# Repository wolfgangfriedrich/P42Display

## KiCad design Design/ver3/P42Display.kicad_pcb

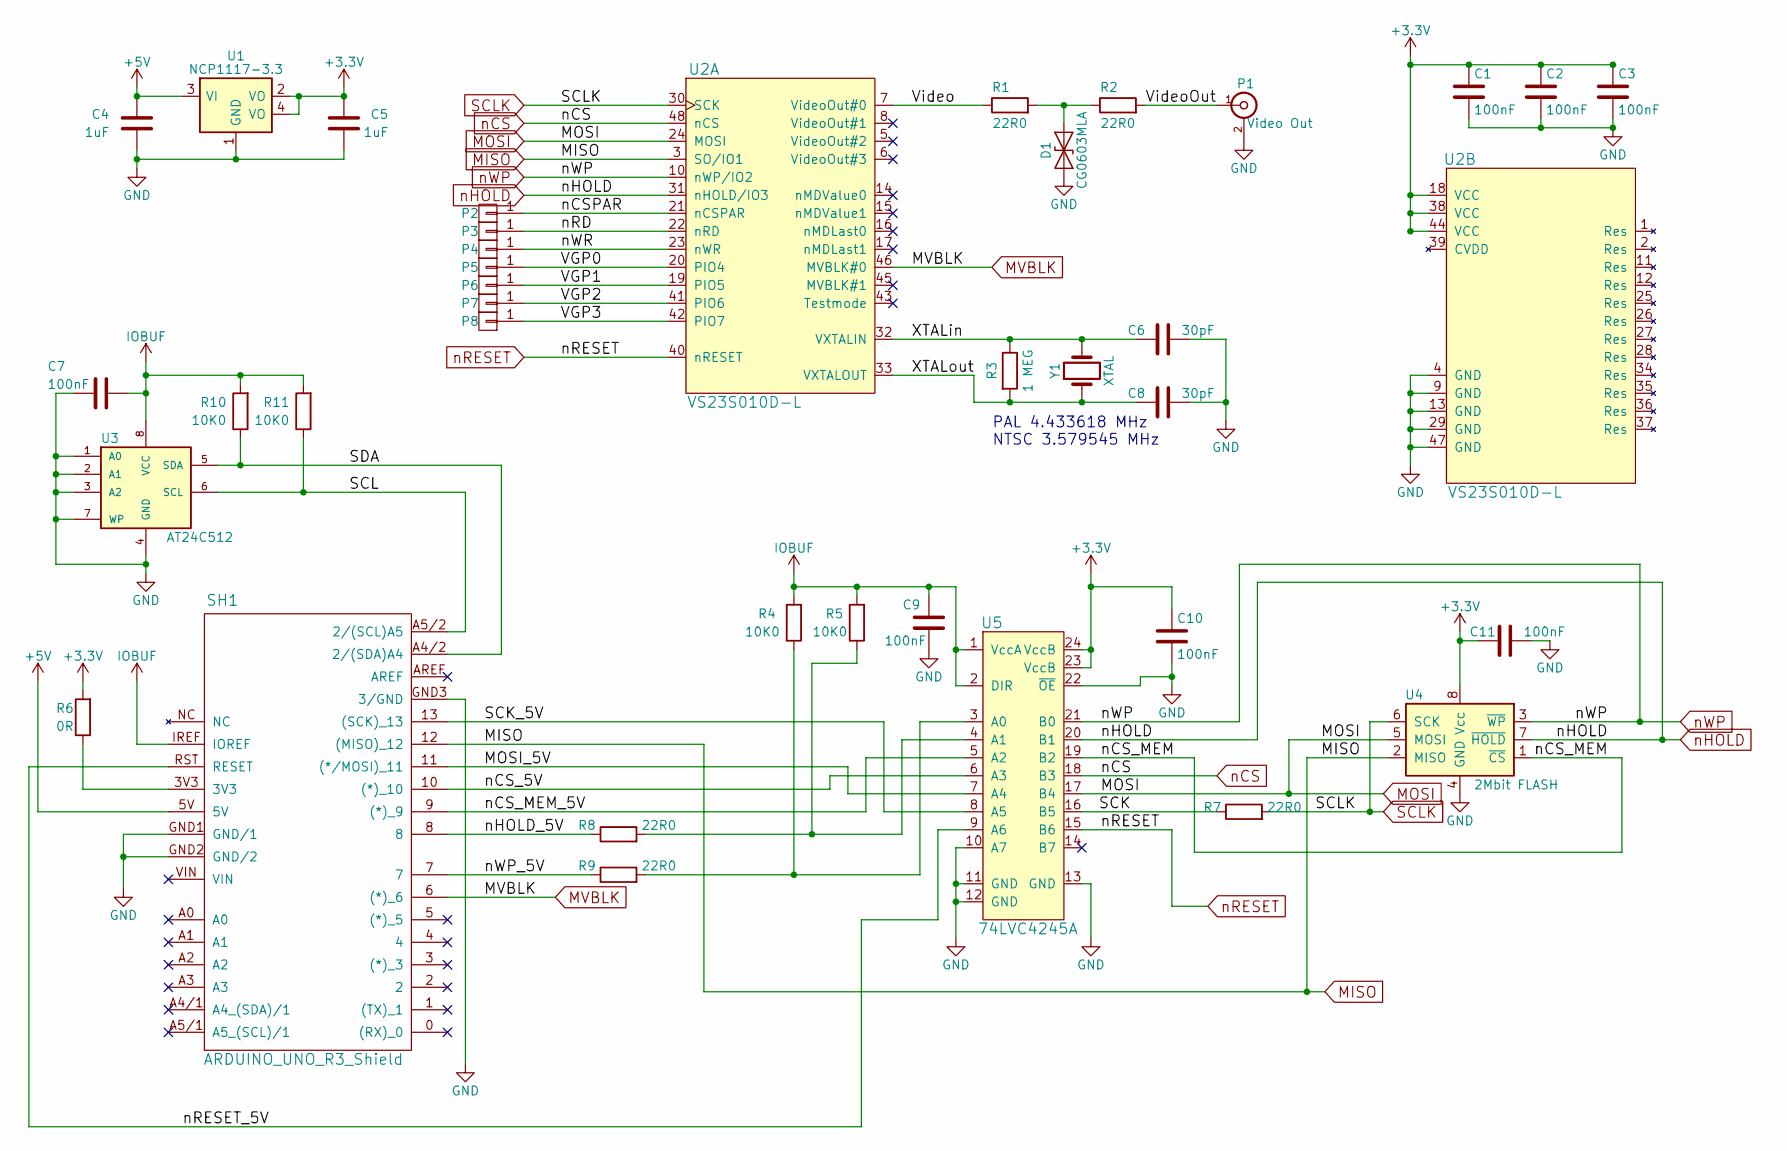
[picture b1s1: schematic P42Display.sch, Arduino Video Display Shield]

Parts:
C1, C2, C3, C7, C9, C10, C11: 100nF; C_0603; Mfr1PN na
C4, C5: 1uF; C_0603; Mfr1PN na
C6, C8: 30pF; C_0603; Mfr1PN na
D1: CG0603MLA; C_0603; Mfr1PN CG0603MLA-5.5ME
P1: Video Out; CUI_RCJ-01x; Mfr1PN RCJ-014
P2: nCS; Measurement_Point_Round-TH_Small
P3: nRD; Measurement_Point_Round-TH_Small
P4: nWR; Measurement_Point_Round-TH_Small
P5: VGP0; Measurement_Point_Round-TH_Small
P6: VGP1; Measurement_Point_Round-TH_Small
P7: VGP2; Measurement_Point_Round-TH_Small
P8: VGP3; Measurement_Point_Round-TH_Small
R1, R2, R7, R8, R9: 22R0; R_0603
R3: 1 MEG; R_0603
R4, R5, R10, R11: 10K0; R_0603
R6: 0R; R_0603
SH1: ARDUINO_UNO_R3_Shield; ARDUINO_as_UNO_R3_CONTOUR
U1: NCP1117-3.3; SOT-223; Mfr1PN AZ1117EH-3.3TRG1
U2: VS23S010D-L; LQFP-48_7x7mm_Pitch0.5mm; Mfr1PN VS23S010D-L
U3: AT24C512; SOIC-8-N; Mfr1PN AT24CS64-SSHM
U4: 2Mbit FLASH; SOIC-8-N; Mfr1PN W25X20CLSNIG
U5: 74LVC4245A; TSSOP-24_4.4x7.8mm_Pitch0.65mm; Mfr1PN 74LVC4245APW
Y1: XTAL; Crystal_SMD_HC49-SD; Mfr1PN ABLS-3.579545MHZ-D-4-T

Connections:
+3V3: C1.1, C2.1, C3.1, C5.2, C10.1, C11.2, R6.2, U1.2 (VO), U1.4 (VO), U2.18 (VCC), U2.38 (VCC), U2.44 (VCC), U4.8 (Vcc), U5.23 (VccB), U5.24 (VccB)
+5V: C4.2, SH1.5V, U1.3 (VI)
/MOSI_5V: SH1.11 ((*/MOSI)_11), U5.7 (A4)
/SCK: R7.1, U5.16 (B5)
/SCK_5V: SH1.13 ((SCK)_13), U5.8 (A5)
/SCL: R11.1, SH1.A5/2 (2/(SCL)A5), U3.6 (SCL)
/SDA: R10.1, SH1.A4/2 (2/(SDA)A4), U3.5 (SDA)
/VGP0: P5.1, U2.20 (PIO4)
/VGP1: P6.1, U2.19 (PIO5)
/VGP2: P7.1, U2.41 (PIO6)
/VGP3: P8.1, U2.42 (PIO7)
/Video: R1.1, U2.7 (VideoOut#0)
/VideoOut: P1.1 (In), R2.2
/XTALin: C6.2, R3.1, U2.32 (VXTALIN), Y1.2
/XTALout: C8.2, R3.2, U2.33 (VXTALOUT), Y1.1
/nCSPAR: P2.1, U2.21 (nCSPAR)
/nCS_5V: SH1.10 ((*)_10), U5.6 (A3)
/nCS_MEM: U4.1 (~CS), U5.19 (B2)
/nCS_MEM_5V: SH1.9 ((*)_9), U5.5 (A2)
/nHOLD_5V: R8.1, SH1.8
/nRD: P3.1, U2.22 (nRD)
/nRESET_5V: SH1.RST (RESET), U5.9 (A6)
/nWP_5V: R9.1, SH1.7
/nWR: P4.1, U2.23 (nWR)
GND: C1.2, C2.2, C3.2, C4.1, C5.1, C6.1, C7.2, C8.1, C9.2, C10.2, C11.1, D1.1 (A1), P1.2 (Ext), SH1.GND1 (GND/1), SH1.GND2 (GND/2), SH1.GND3 (3/GND), U1.1 (GND), U2.4 (GND), U2.9 (GND), U2.13 (GND), U2.29 (GND), U2.47 (GND), U3.1 (A0), U3.2 (A1), U3.3 (A2), U3.4 (GND), U3.7 (WP), U4.4 (GND), U5.10 (A7), U5.11 (GND), U5.12 (GND), U5.13 (GND), U5.22 (~OE)
IOBUF: C7.1, C9.1, R4.2, R5.2, R10.2, R11.2, SH1.IREF (IOREF), U3.8 (VCC), U5.1 (VccA), U5.2 (DIR)
MISO: SH1.12 ((MISO)_12), U2.3 (SO/IO1), U4.2 (MISO)
MOSI: U2.24 (MOSI), U4.5 (MOSI), U5.17 (B4)
MVBLK: SH1.6 ((*)_6), U2.46 (MVBLK#0)
unnamed: D1.2 (A2), R1.2, R2.1
unnamed: R4.1, R9.2, U5.3 (A0)
unnamed: R5.1, R8.2, U5.4 (A1)
unnamed: R6.1, SH1.3V3
SCLK: R7.2, U2.30 (SCK), U4.6 (SCK)
nCS: U2.48 (nCS), U5.18 (B3)
nHOLD: U2.31 (nHOLD/IO3), U4.7 (~HOLD), U5.20 (B1)
nRESET: U2.40 (nRESET), U5.15 (B6)
nWP: U2.10 (nWP/IO2), U4.3 (~WP), U5.21 (B0)

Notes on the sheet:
PAL 4.433618 MHz NTSC 3.579545 MHz

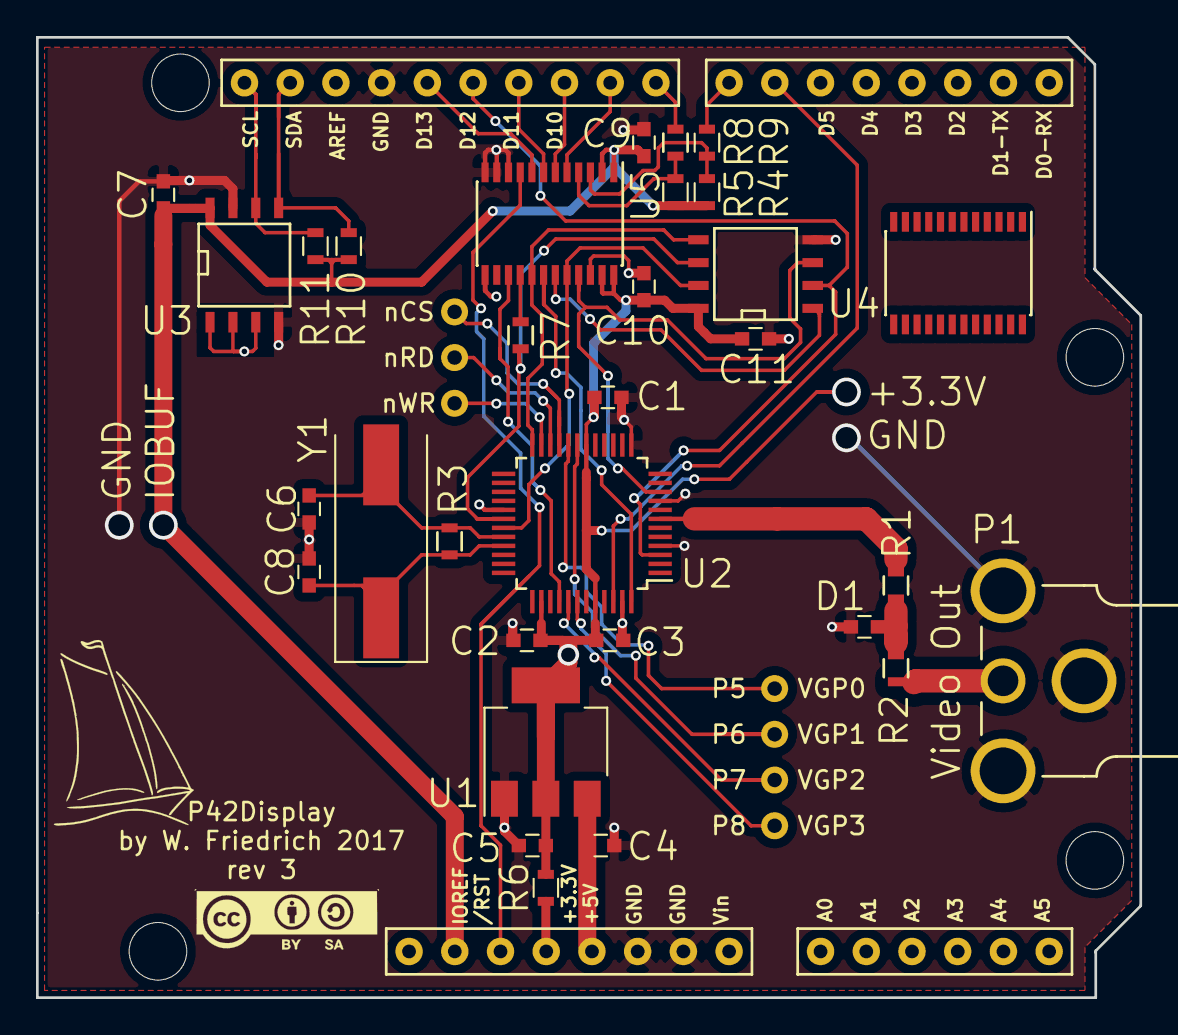
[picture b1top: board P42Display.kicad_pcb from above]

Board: 2 copper layers, 61.3 x 53.3 mm, 38 parts (0 on the bottom side), 38 nets.

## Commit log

2017-04-17 :lollipop: Added .gitattributes & .gitignore files
2017-04-17 Arduino Display Shield
    Shield with Framebuffer and analog video output
2018-01-01 SCH rev3 added
    Rev3 with SPI FLASH and IOBUF usage
2018-01-01 Revert "SCH rev3 added"
    This reverts commit 6ab0f006407915276edc94fd56155b677fc2c638.
2018-01-01 Schematics rev 3 added
    Sch rev 3 with SPI FLASH and IOBUF for voltage level shifter
2018-02-18 Added Memtest code
    Arduino program to test I2C EEPROM and SPI Flash. And added font bitmap
    information into Flash.
2018-03-10 Initial files for Tindie sale start
    Rev3 KiCAD files, demo SW and documentation
2018-03-10 Update with license on board
2018-03-26 V1.1 update
    Due SPI connector description
2018-03-27 2nd attempt to fix Due/Mega pin connection
    Mega/Due pins and wire colour update
2018-04-05 Code update
    Memtest and Demo code with boingball animation
2018-04-05 Documentation added extended memory map
    and name cleanup
2018-04-05 Delete P42 Arduino Display Shield(rev3) Documentation .pdf
    Fixed name in other file
2019-06-29 Update documentation
    New Tindie Store Adress
2019-08-13 Image display
    WIP functionality to store an image in Flash received over UART
    (Memtest). Display image from Flash in Demo. Works with 256 colour BMP
    displayed in grey scale.
2019-11-30 Added doc for Arduino DUE
    Instructions how to plug the shield into a DUE.
2019-12-08 Debug update
    Memtest and Display_demo: added some debug updates and re-aranged
    memtest for more secure operation
2020-06-06 Character map in video memory
    Test to load the character map into video memory instead of Flash.

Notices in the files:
Design/ver3/P42Display.kicad_pcb:
Creative Commons Attribution-ShareAlike 4.0 International License
This work is licensed under
